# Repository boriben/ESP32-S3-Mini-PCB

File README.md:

# ESP32-S3-Mini-PCB
I had a s3 mini module laying around, so I decided to design a board for it. Now I have even more s3 minis laying around :D
I learned a lot from this project!

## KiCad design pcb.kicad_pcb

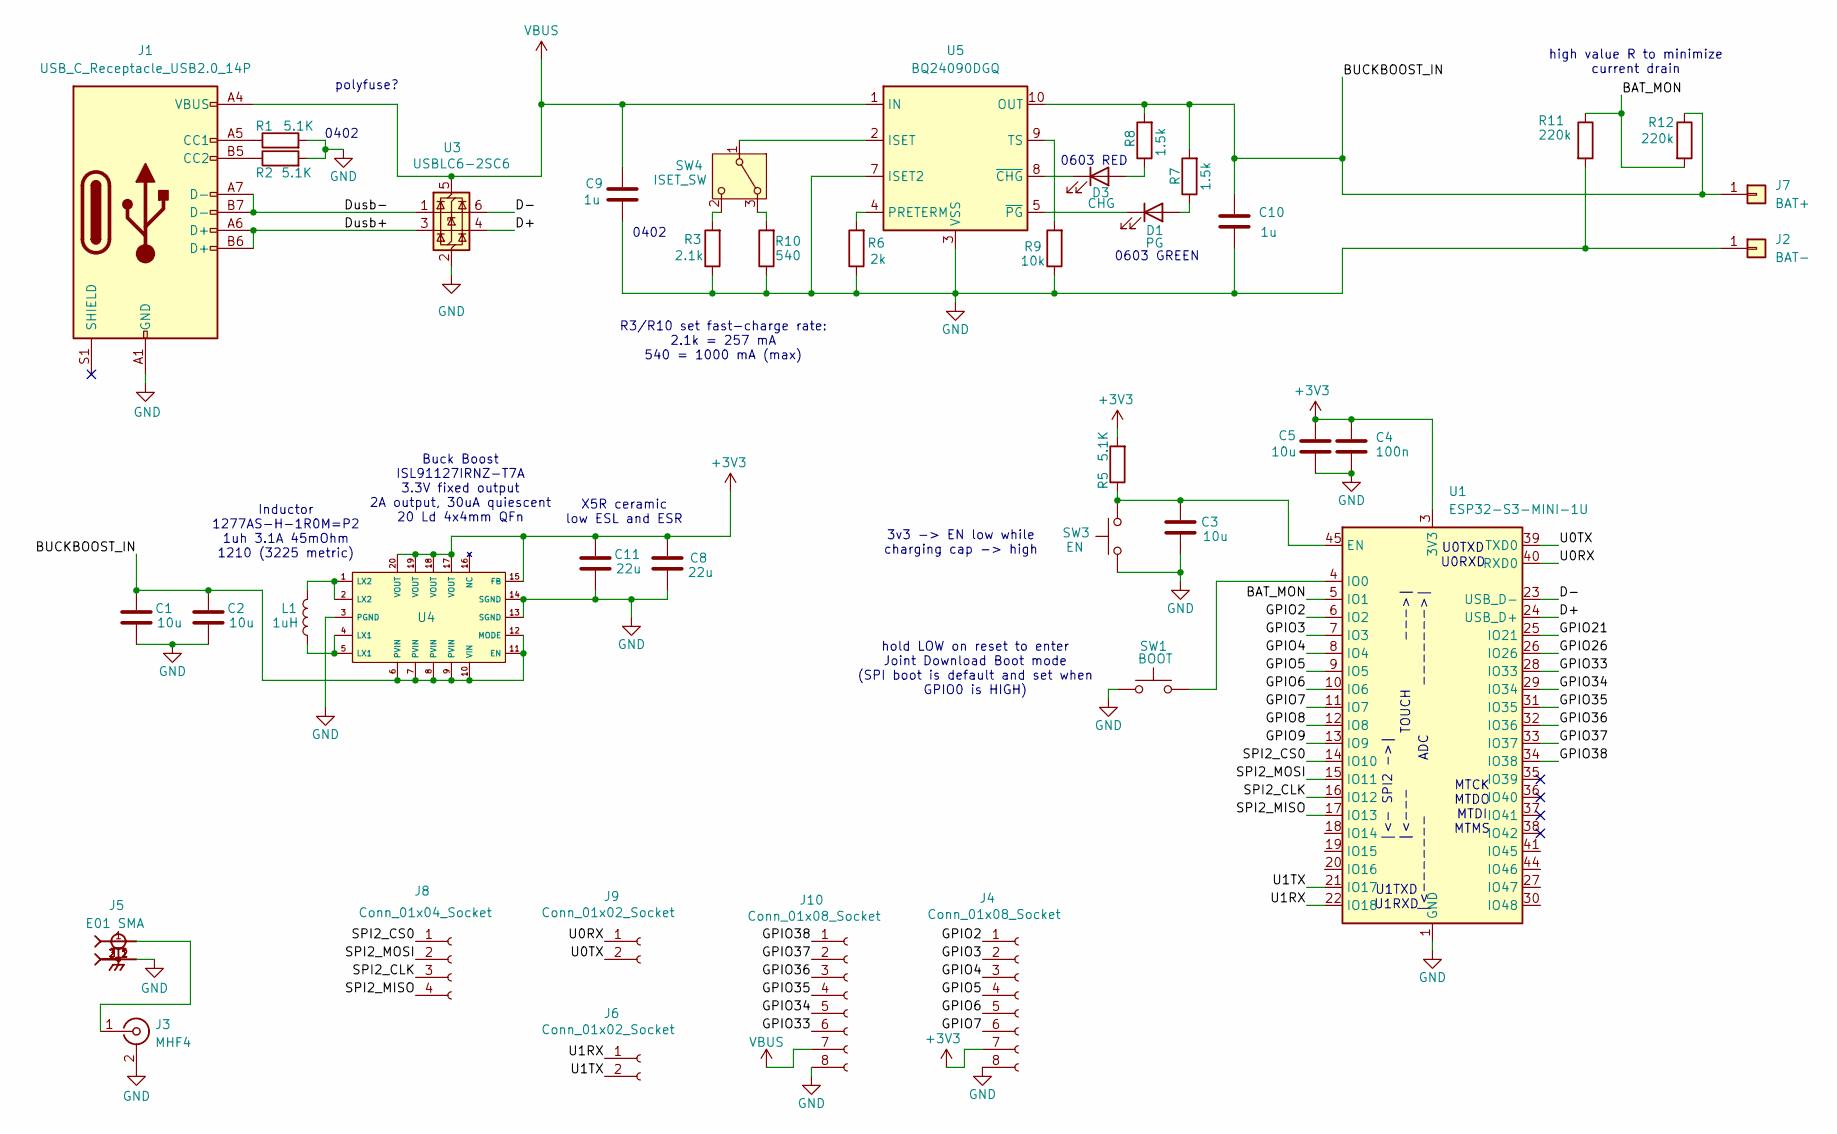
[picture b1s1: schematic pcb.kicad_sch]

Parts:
C1, C2: 10u; C_0603_1608Metric
C3, C5: 10u; C_0402_1005Metric
C4: 100n; C_0402_1005Metric
C8, C11: 22u; C_0603_1608Metric
C9, C10: 1u; C_0402_1005Metric
D1: PG; LED_0603_1608Metric
D3: CHG; LED_0603_1608Metric
J1: USB_C_Receptacle_USB2.0_14P; USB_C_Receptacle_G-Switch_GT-USB-7010ASV
J2: BAT-; PinHeader_1x01_P2.54mm_Vertical
J3: MHF4; IPEX_20449-001E-03
J4, J10: Conn_01x08_Socket; PinHeader_1x08_P2.54mm_Vertical
J5: E01 SMA; SAMTEC_SMA-J-P-H-ST-EM1; PARTREV G
J6, J9: Conn_01x02_Socket; PinHeader_1x02_P2.54mm_Vertical
J7: BAT+; PinHeader_1x01_P2.54mm_Vertical
J8: Conn_01x04_Socket; PinHeader_1x04_P2.54mm_Vertical
L1: 1uH; 1277AS-H-1R0M=P2
R1, R2, R5: 5.1K; R_0402_1005Metric
R3: 2.1k; R_0402_1005Metric
R6: 2k; R_0402_1005Metric
R7, R8: 1.5k; R_0402_1005Metric
R9: 10k; R_0402_1005Metric
R10: 540; R_0402_1005Metric
R11, R12: 220k; R_0402_1005Metric
SW1: BOOT; 3x4x2mm button
SW3: EN; 3x4x2mm button
SW4: ISET_SW; SW_Slide-03_Wuerth-WS-SLTV_10x2.5x6.4_P2.54mm
U1: ESP32-S3-MINI-1U; ESP32-S2-MINI-1U
U3: USBLC6-2SC6; SOT-23-6
U4: QFN-20-1EP_4x4mm_P0.5mm_EP2.5x2.5mm
U5: BQ24090DGQ; HVSSOP-10-1EP_3x3mm_P0.5mm_EP1.57x1.88mm_ThermalVias

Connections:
+3V3: C4.1, C5.1, C8.1, C11.1, J4.7, R5.2, U1.3 (3V3), U4.15 (FB), U4.17 (VOUT), U4.18 (VOUT), U4.19 (VOUT), U4.20 (VOUT)
/BAT_MON: R11.1, R12.2, U1.5 (IO1)
/BUCKBOOST_IN: C1.1, C2.1, C10.1, J7.1, R7.2, R8.2, R12.1, U4.6 (PVIN), U4.7 (PVIN), U4.8 (PVIN), U4.9 (PVIN), U4.10 (VIN), U4.11 (EN), U4.12 (MODE), U5.10 (OUT)
/D+: U1.24 (USB_D+), U3.4 (I/O2)
/D-: U1.23 (USB_D-), U3.6 (I/O1)
/Dusb+: J1.A6 (D+), J1.B6 (D+), U3.3 (I/O2)
/Dusb-: J1.A7 (D-), J1.B7 (D-), U3.1 (I/O1)
/GPIO2: J4.1, U1.6 (IO2)
/GPIO3: J4.2, U1.7 (IO3)
/GPIO4: J4.3, U1.8 (IO4)
/GPIO5: J4.4, U1.9 (IO5)
/GPIO6: J4.5, U1.10 (IO6)
/GPIO7: J4.6, U1.11 (IO7)
/GPIO8: U1.12 (IO8)
/GPIO9: U1.13 (IO9)
/GPIO21: U1.25 (IO21)
/GPIO26: U1.26 (IO26)
/GPIO33: J10.6, U1.28 (IO33)
/GPIO34: J10.5, U1.29 (IO34)
/GPIO35: J10.4, U1.31 (IO35)
/GPIO36: J10.3, U1.32 (IO36)
/GPIO37: J10.2, U1.33 (IO37)
/GPIO38: J10.1, U1.34 (IO38)
/SPI2_CLK: J8.3, U1.16 (IO12)
/SPI2_CS0: J8.1, U1.14 (IO10)
/SPI2_MISO: J8.4, U1.17 (IO13)
/SPI2_MOSI: J8.2, U1.15 (IO11)
/U0RX: J9.1, U1.40 (RXD0)
/U0TX: J9.2, U1.39 (TXD0)
/U1RX: J6.1, U1.22 (IO18)
/U1TX: J6.2, U1.21 (IO17)
GND: C1.2, C2.2, C3.2, C4.2, C5.2, C8.2, C9.2, C10.2, C11.2, J1.A1 (GND), J1.A12 (GND), J1.B1 (GND), J1.B12 (GND), J2.1, J3.2 (Ext), J4.8, J5.2_1, J5.2_2, J5.3_1, J5.3_2, J10.8, R1.2, R2.2, R3.1, R6.1, R9.1, R10.1, R11.2, SW1.1, SW3.1, U1.1 (GND), U1.2 (GND), U1.42 (GND), U1.43 (GND), U1.46 (GND), U1.47 (GND), U1.48 (GND), U1.49 (GND), U1.50 (GND), U1.51 (GND), U1.52 (GND), U1.53 (GND), U1.54 (GND), U1.55 (GND), U1.56 (GND), U1.57 (GND), U1.58 (GND), U1.59 (GND), U1.60 (GND), U1.61 (GND), U1.62 (GND), U1.63 (GND), U1.64 (GND), U1.65 (GND), U3.2 (GND), U4.3 (PGND), U4.13 (SGND), U4.14 (SGND), U4.21, U5.3 (VSS), U5.7 (ISET2), U5.11 (VSS)
unnamed: D1.2 (A), R7.1
unnamed: D1.1 (K), U5.5 (~PG)
unnamed: D3.2 (A), R8.1
unnamed: D3.1 (K), U5.8 (~CHG)
unnamed: J1.A5 (CC1), R1.1
unnamed: J1.B5 (CC2), R2.1
unnamed: J3.1 (In), J5.1
unnamed: L1.1, U4.4 (LX1), U4.5 (LX1)
unnamed: L1.2, U4.1 (LX2), U4.2 (LX2)
unnamed: R10.2, SW4.3 (A)
unnamed: SW4.1 (B), U5.2 (ISET)
unnamed: R3.2, SW4.2 (C)
unnamed: C3.1, R5.1, SW3.2, U1.45 (EN)
unnamed: SW1.2, U1.4 (IO0)
unnamed: R6.2, U5.4 (PRETERM)
unnamed: R9.2, U5.9 (TS)
VBUS: C9.1, J1.A4 (VBUS), J1.A9 (VBUS), J1.B4 (VBUS), J1.B9 (VBUS), J10.7, U3.5 (VBUS), U5.1 (IN)

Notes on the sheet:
Buck Boost ISL91127IRNZ-T7A 3.3V fixed output 2A output, 30uA quiescent 20 Ld 4x4mm QFn
polyfuse?
|<--- TOUCH --->|
3v3 -> EN low while charging cap -> high
high value R to minimize current drain
X5R ceramic low ESL and ESR
0402
U0TXD U0RXD
|<------- ADC ------->|
U1TXD U1RXD
hold LOW on reset to enter Joint Download Boot mode (SPI boot is default and set when GPIO0 is HIGH)
R3/R10 set fast-charge rate: 2.1k = 257 mA 540 = 1000 mA (max)
|<- SPI2 ->|
Inductor 1277AS-H-1R0M=P2 1uh 3.1A 45mOhm 1210 (3225 metric)
0603 GREEN
0603 RED
MTCK MTDO MTDI MTMS

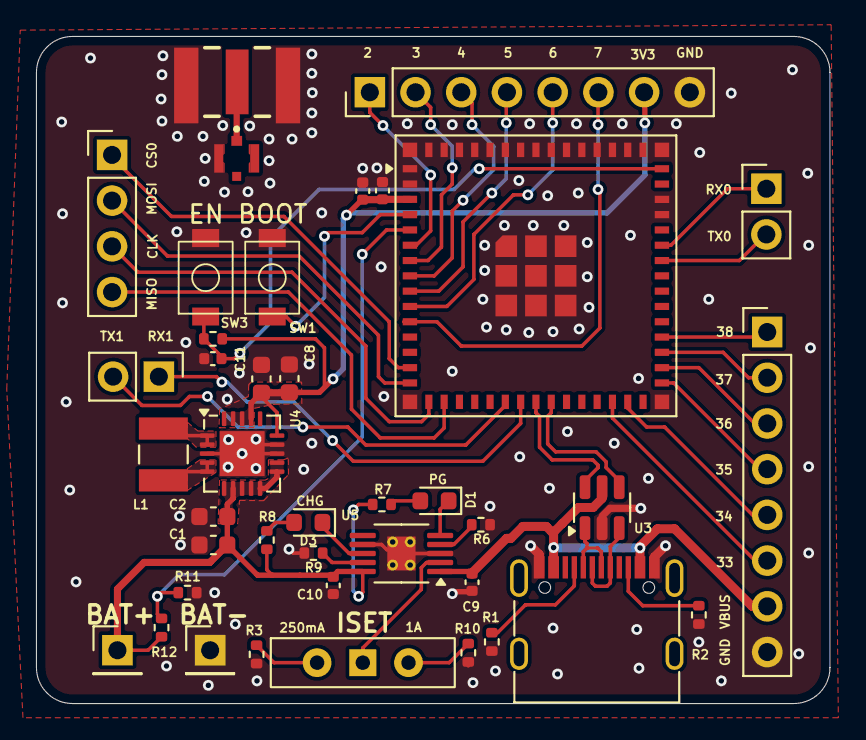
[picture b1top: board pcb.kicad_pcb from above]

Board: 4 copper layers, 44.1 x 37.1 mm, 40 parts (0 on the bottom side), 45 nets.

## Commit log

2026-01-13 init commit
2026-01-14 removed files from git
2026-02-12 Remove ignored files from tracking
2026-02-12 change .gitignore
